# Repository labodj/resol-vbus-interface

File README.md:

# RESOL VBus interface

I designed this board to connect my **RESOL DeltaSol CS Plus** solar controller to
ESPHome and Home Assistant, with hardware for both receiving and transmitting
VBus messages.

Both versions use a socketed **LOLIN D1 mini or S3 Mini**, a 5 V supply and the same RX/TX firmware pin mapping. Choose the board by how the controller and ESP must be grounded.

| | Isolated (Rev E design files) | ECO Rev A |
|---|---|---|
| Power and UART | RECOM isolated DC/DC, bus-side regulator and digital isolator | Receiver and TX logic run from the module’s 3.3 V rail |
| Grounding | ESP/USB ground is separated from the VBus circuit | USB, J1 ground and the negative output of the VBus bridge are connected |
| Assembly | 35 SMT components | 26 SMT components |
| Test status | D1 mini and S3 Mini tested on reworked Rev D; S3 Mini in service for weeks on a DeltaSol CS Plus | CAD checks passed; first assembled-board and field tests are pending |
| KiCad and schematic | [Project](hardware/rev-e/Resol_VBus_RevE.kicad_pro) · [PDF](docs/schematic.pdf) | [Project](hardware/eco-rev-a/RESOL_VBus_ECO_RevA.kicad_pro) · [PDF](hardware/eco-rev-a/RESOL_VBus_ECO_RevA.pdf) |
| Fabrication | [Gerber ZIP](fabrication/Resol_VBus_RevE_Gerbers.zip) · [BOM](fabrication/bom.csv) · [CPL](fabrication/cpl.csv) | [Gerber + stencil ZIP](fabrication/eco-rev-a/RESOL_VBus_ECO_RevA_Gerbers.zip) · [BOM](hardware/eco-rev-a/BOM.csv) · [CPL](fabrication/eco-rev-a/cpl.csv) |

Choose the isolated board when the grounding of the controller or a USB-connected PC is unknown. Choose ECO when a common ground is acceptable. On both boards, power from **J1 or USB, one source at a time**. J1 and J2 use identical connectors; label the power and VBus cables.

| KiCad 3D view | Isolated Rev E | ECO Rev A |
|---|---|---|
| Front |  |  |
| Back |  |  |

The photograph below shows the earlier isolated prototype used in the installation.

## Build notes

- **Isolated:** [prototype release](https://github.com/labodj/resol-vbus-interface/releases/tag/rev-e-prototype-1), [fabrication](docs/fabrication.md), [assembly](docs/assembly.md) and [circuit description](docs/circuit.md).
- **ECO:** [fabrication package and checks](fabrication/eco-rev-a/README.md), [wiring and first power-up](hardware/eco-rev-a/README.md).

## Rev E at a glance

- Two layers, **64 x 50 mm**, with SMD parts on the front.
- Isolated power, RX and TX, independent of the VBus supply level.
- TX stays off during startup and low isolated-supply voltage.
- Replaceable ESP module and accessible test points.
- JST XH **B2B-XH-A, 2.50 mm** connectors for both external power and VBus.
- TS391RIYLT receiver with hysteresis and input filtering.

**J1 is the 5 V input; J2 is VBus.** The connectors are identical, so label the
cables. Use either USB power or external 5 V, **never both at once**. Keep
`GND` and `GND_ISO` separate. This is a low-voltage interface, not a mains input.

## Field experience

The target controller is a DeltaSol CS Plus running firmware 1.11, with an
approximately 20 cm VBus cable.

The photographed board is the isolated Rev D with the comparator wiring corrected by hand. Both modules worked on this board. The [validation record](docs/validation.md) describes the correction in the later isolated layouts and the checks on the published Rev E files.

## Firmware

VBus uses UART at **9600 baud, 8N1, non-inverted**. TX must idle HIGH; driving it
LOW enables the bus sink once the bus-side supervisor releases the TX inhibit. Firmware must wait
for a bus grant before transmitting.

| Module | RX GPIO | TX GPIO | Observed on reworked Rev D |
|---|---:|---:|---|
| LOLIN D1 mini v4.0.0 (ESP8266) | 13 | 12 | Tested and working |
| LOLIN S3 Mini v1.0.0 | 11 | 13 | In service for weeks |

I am developing the ESPHome TX support separately. This repository contains
the hardware, not a ready-to-flash firmware image. It does not imply that the
standard ESPHome VBus component already supports transmitting settings.

## Editing the design

Install KiCad 10 or newer with its standard libraries and open the `.kicad_pro`
file. Project libraries use relative paths. The optional RECOM 3D model is not
included; a missing model affects the 3D view only. See [third-party notices](THIRD_PARTY.md).

The [maintenance notes](docs/manual-review.md) explain test-point exclusions
and the checks to run after changes.

## Citation

If you use this design in a publication, cite it using the [project citation metadata](CITATION.cff). Include the board revision so readers can identify the circuit you used.

## Background and license

My original design drew on the [ESPHome VBus documentation](https://esphome.io/components/vbus/)
and [FatBeard's VBus PCB project](https://github.com/FatBeard/vbus-arduino-library/tree/master/pcb).
This is an independent project, without endorsement by RESOL, ESPHome or LOLIN.
Their names and trademarks remain theirs.

Original hardware: **CERN-OHL-P-2.0**; documentation: **CC-BY-4.0**; scripts:
**MIT**. KiCad library data retains **CC-BY-SA-4.0 with the KiCad library exception**.
See [LICENSE.md](LICENSE.md) and [third-party notices](THIRD_PARTY.md).

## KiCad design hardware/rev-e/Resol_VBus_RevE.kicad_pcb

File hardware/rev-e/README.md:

# RESOL VBus isolated interface, Rev E

The RECOM converter and the UART isolator separate the controller-side circuit from the ESP supply and USB ground. Both external 5 V and USB can power the interface. Use one source at a time.

Both the D1 mini and the S3 Mini worked on the isolated Rev D after the comparator wiring rework. The S3 Mini has operated for weeks on a DeltaSol CS Plus. The published Rev E files have their own [CAD validation record](../../docs/validation.md).

| Front | Back |
|---|---|
|  |  |

[KiCad project](Resol_VBus_RevE.kicad_pro) · [Schematic](../../docs/schematic.pdf) · [Fabrication files](../../docs/fabrication.md) · [Assembly guide](../../docs/assembly.md)

The [ECO Rev A](../eco-rev-a/README.md) uses the module’s 3.3 V supply and a shared ground. It has its own fabrication package and is awaiting hardware testing.

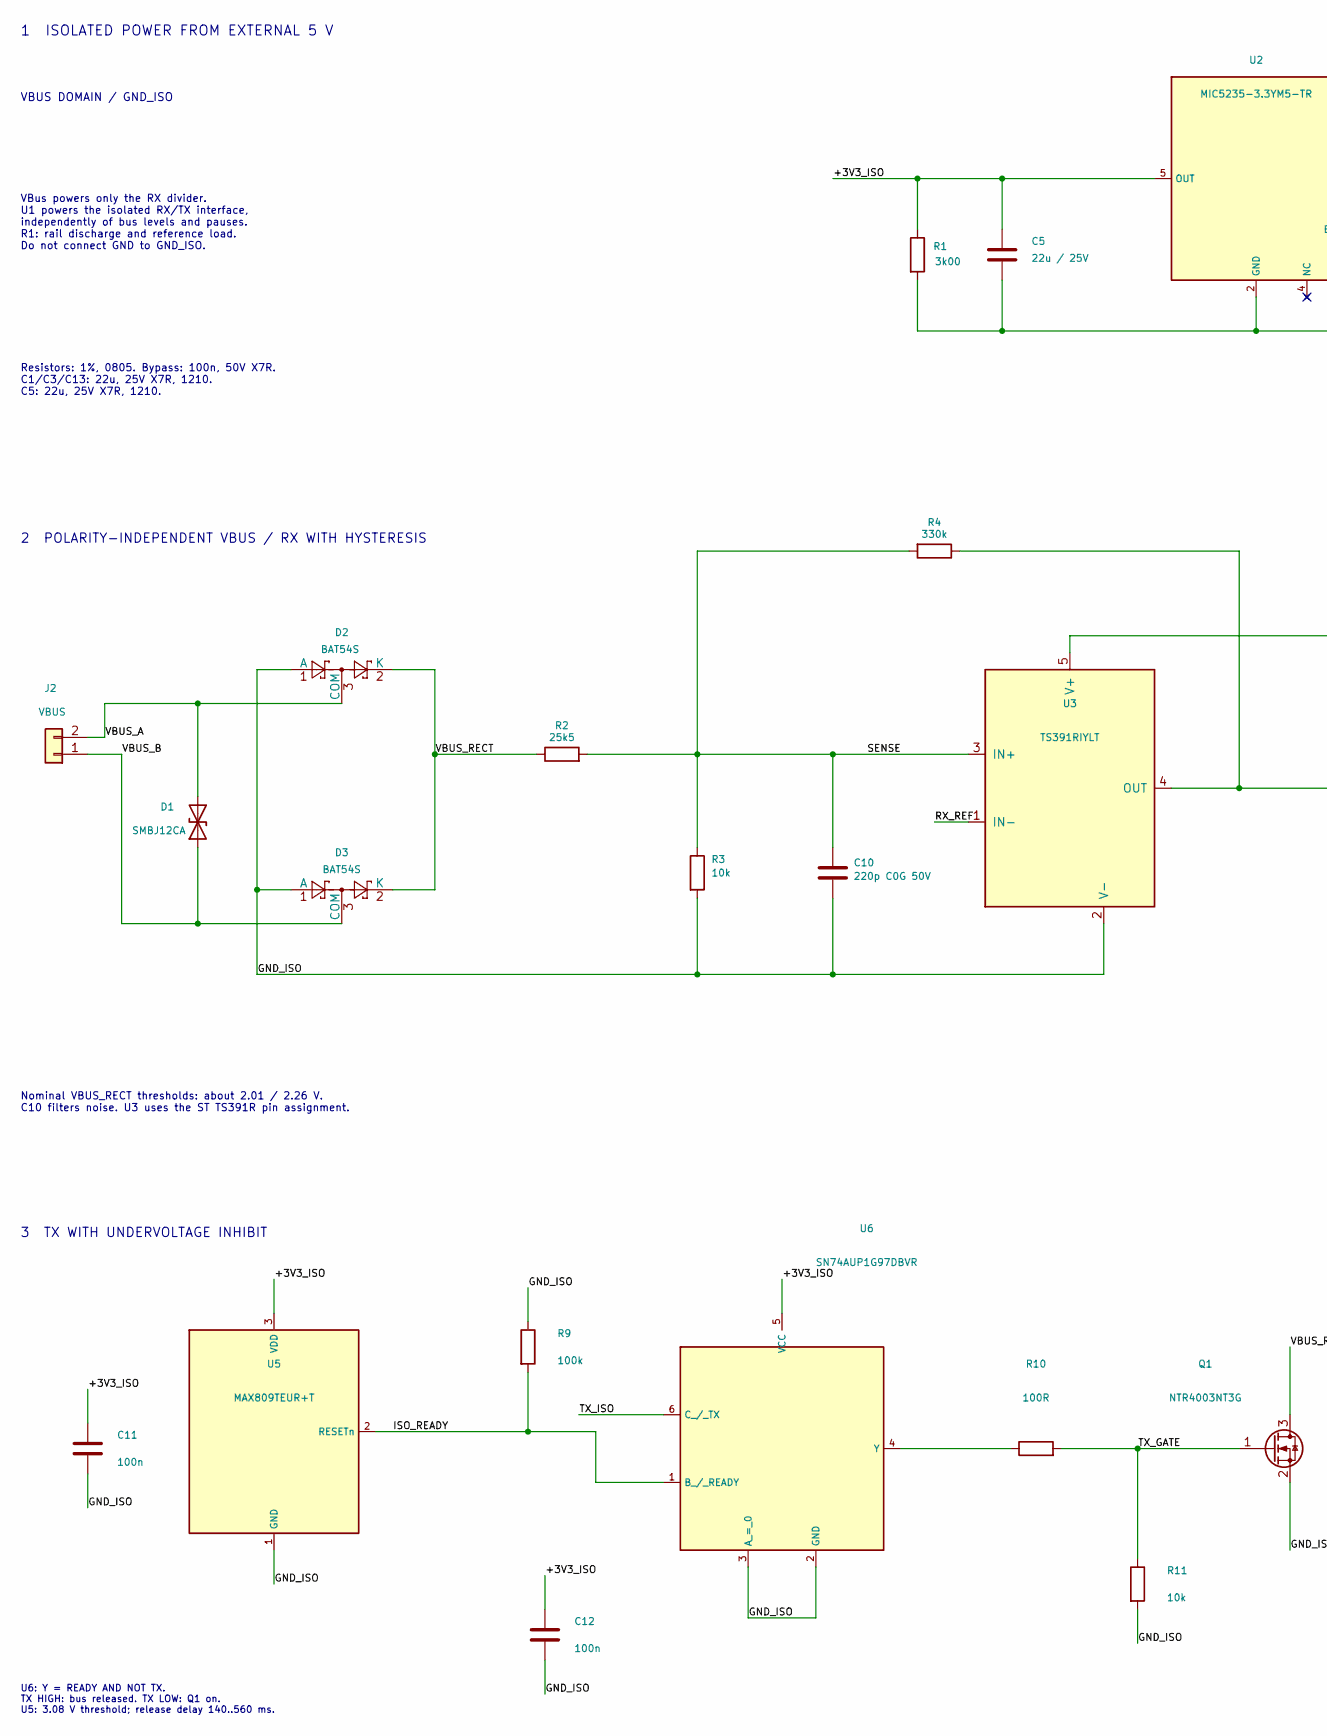
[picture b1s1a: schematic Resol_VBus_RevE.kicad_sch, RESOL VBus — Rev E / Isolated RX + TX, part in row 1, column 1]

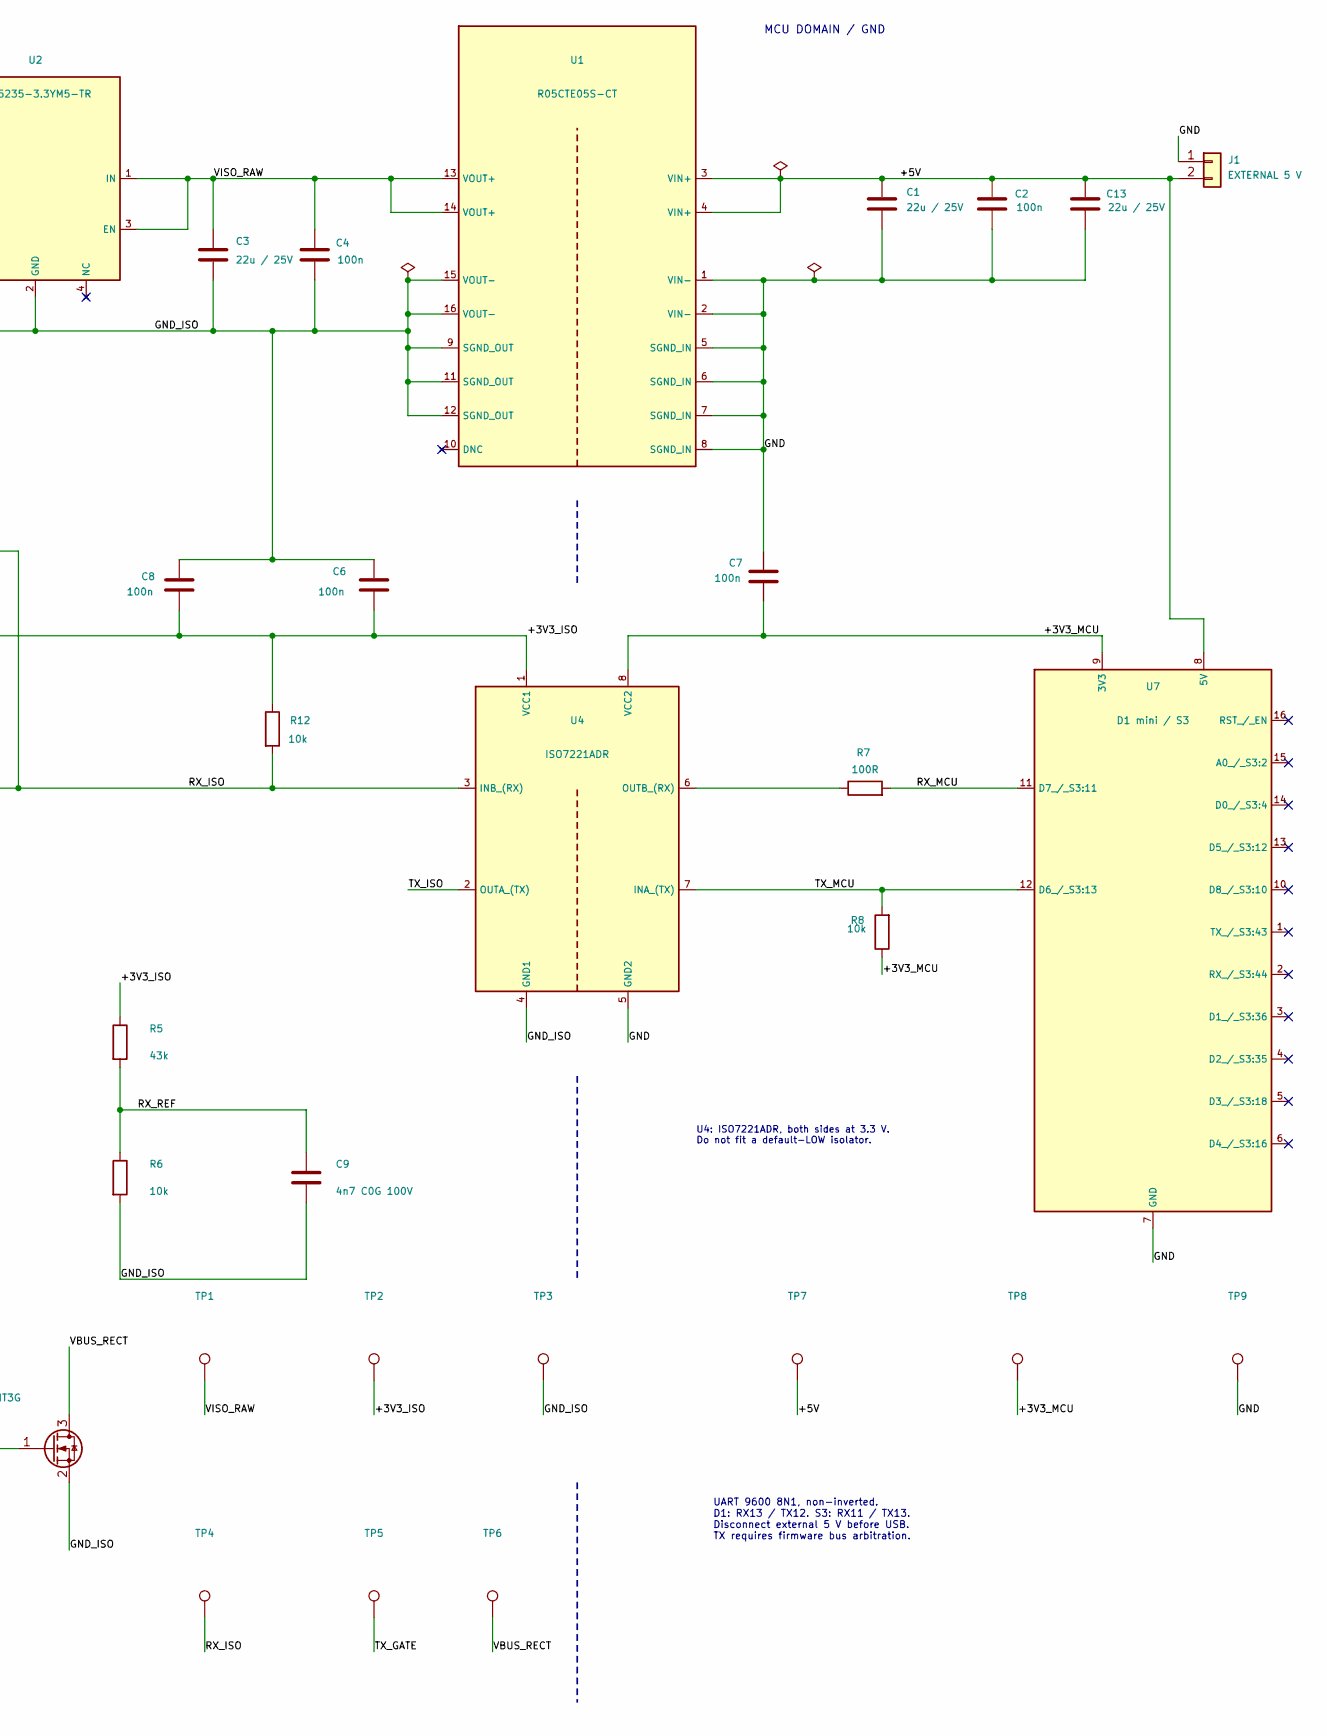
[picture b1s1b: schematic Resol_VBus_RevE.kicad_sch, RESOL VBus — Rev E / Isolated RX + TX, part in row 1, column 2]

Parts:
C1, C3, C5, C13: 22u / 25V; C_1210_3225Metric; MPN CL32B226KAJNNNE
C2, C4, C6, C7, C8, C11, C12: 100n; C_0805_2012Metric; MPN CC0805KRX7R9BB104
C9: 4n7 C0G 100V; C_0805_2012Metric; MPN C0805C472J1GACTU
C10: 220p C0G 50V; C_0805_2012Metric; MPN C0805C221J5GACTU
D1: SMBJ12CA; D_SMB; MPN SMBJ12CA-E3/52
D2, D3: BAT54S; SOT-23; MPN BAT54SQ-7-F
J1: EXTERNAL 5 V; JST_XH_B2B-XH-A_1x02_P2.50mm_Vertical; MPN B2B-XH-A
J2: VBUS; JST_XH_B2B-XH-A_1x02_P2.50mm_Vertical; MPN B2B-XH-A
Q1: NTR4003NT3G; SOT-23; MPN NTR4003NT3G
R1: 3k00; R_0805_2012Metric; MPN RC0805FR-073KL
R2: 25k5; R_0805_2012Metric; MPN RC0805FR-0725K5L
R3, R6, R8, R11, R12: 10k; R_0805_2012Metric; MPN RC0805FR-0710KL
R4: 330k; R_0805_2012Metric; MPN RC0805FR-07330KL
R5: 43k; R_0805_2012Metric; MPN RC0805FR-0743KL
R7, R10: 100R; R_0805_2012Metric; MPN RC0805FR-07100RL
R9: 100k; R_0805_2012Metric; MPN RC0805FR-07100KL
TP1: VISO_RAW; TestPoint_Pad_D1.0mm
TP2: +3V3_ISO; TestPoint_Pad_D1.0mm
TP3: GND_ISO; TestPoint_Pad_D1.0mm
TP4: RX_ISO; TestPoint_Pad_D1.0mm
TP5: TX_GATE; TestPoint_Pad_D1.0mm
TP6: VBUS_RECT; TestPoint_Pad_D1.0mm
TP7: +5V; TestPoint_Pad_D1.0mm
TP8: +3V3_MCU; TestPoint_Pad_D1.0mm
TP9: GND; TestPoint_Pad_D1.0mm
U1: R05CTE05S-CT; RECOM_R05CTE05S; MPN R05CTE05S-CT
U2: MIC5235-3.3YM5-TR; SOT-23-5; MPN MIC5235-3.3YM5-TR
U3: TS391RIYLT; SOT-23-5; MPN TS391RIYLT
U4: ISO7221ADR; SOIC-8_3.9x4.9mm_P1.27mm; MPN ISO7221ADR
U5: MAX809TEUR+T; SOT-23; MPN MAX809TEUR+T
U6: SN74AUP1G97DBVR; SOT-23-6; MPN SN74AUP1G97DBVR
U7: D1 mini / S3; Wemos_D1_mini_2x08

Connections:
/+3V3_ISO: C5.1, C6.1, C8.1, C11.1, C12.1, R1.1, R5.1, R12.1, TP2.1 (1_1), U2.5 (OUT), U3.5 (V+), U4.1 (VCC1), U5.3 (VDD), U6.5 (VCC)
/+3V3_MCU: C7.1, R8.1, TP8.1 (1_1), U4.8 (VCC2), U7.9 (3V3)
/+5V: C1.1, C2.1, C13.1, J1.2, TP7.1 (1_1), U1.3 (VIN+), U1.4 (VIN+), U7.8 (5V)
/GND: C1.2, C2.2, C7.2, C13.2, J1.1, TP9.1 (1_1), U1.1 (VIN-), U1.2 (VIN-), U1.5 (SGND_IN), U1.6 (SGND_IN), U1.7 (SGND_IN), U1.8 (SGND_IN), U4.5 (GND2), U7.7 (GND)
/GND_ISO: C3.2, C4.2, C5.2, C6.2, C8.2, C9.2, C10.2, C11.2, C12.2, D2.1 (A), D3.1 (A), Q1.2 (S), R1.2, R3.2, R6.2, R9.1, R11.2, TP3.1 (1_1), U1.9 (SGND_OUT), U1.11 (SGND_OUT), U1.12 (SGND_OUT), U1.15 (VOUT-), U1.16 (VOUT-), U2.2 (GND), U3.2 (V-), U4.4 (GND1), U5.1 (GND), U6.2 (GND), U6.3 (A_=_0)
/ISO_READY: R9.2, U5.2 (RESETn), U6.1 (B_/_READY)
/RX_ISO: R4.1, R12.2, TP4.1 (1_1), U3.4 (OUT), U4.3 (INB_(RX))
/RX_MCU: R7.2, U7.11 (D7_/_S3:11)
/RX_REF: C9.1, R5.2, R6.1, U3.1 (IN-)
/SENSE: C10.1, R2.2, R3.1, R4.2, U3.3 (IN+)
/TX_GATE: Q1.1 (G), R10.2, R11.1, TP5.1 (1_1)
/TX_ISO: U4.2 (OUTA_(TX)), U6.6 (C_/_TX)
/TX_MCU: R8.2, U4.7 (INA_(TX)), U7.12 (D6_/_S3:13)
/VBUS_A: D1.2 (A2), D2.3 (COM), J2.2
/VBUS_B: D1.1 (A1), D3.3 (COM), J2.1
/VBUS_RECT: D2.2 (K), D3.2 (K), Q1.3 (D), R2.1, TP6.1 (1_1)
/VISO_RAW: C3.1, C4.1, TP1.1 (1_1), U1.13 (VOUT+), U1.14 (VOUT+), U2.1 (IN), U2.3 (EN)
unnamed: R7.1, U4.6 (OUTB_(RX))
unnamed: R10.1, U6.4 (Y)

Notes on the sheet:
2 POLARITY-INDEPENDENT VBUS / RX WITH HYSTERESIS
Resistors: 1%, 0805. Bypass: 100n, 50V X7R. C1/C3/C13: 22u, 25V X7R, 1210. C5: 22u, 25V X7R, 1210.
UART 9600 8N1, non-inverted. D1: RX13 / TX12. S3: RX11 / TX13. Disconnect external 5 V before USB. TX requires firmware bus arbitration.
3 TX WITH UNDERVOLTAGE INHIBIT
Nominal VBUS_RECT thresholds: about 2.01 / 2.26 V. C10 filters noise. U3 uses the ST TS391R pin assignment.
MCU DOMAIN / GND
VBUS DOMAIN / GND_ISO
1 ISOLATED POWER FROM EXTERNAL 5 V
U4: ISO7221ADR, both sides at 3.3 V. Do not fit a default-LOW isolator.
U6: Y = READY AND NOT TX. TX HIGH: bus released. TX LOW: Q1 on. U5: 3.08 V threshold; release delay 140..560 ms.
VBus powers only the RX divider. U1 powers the isolated RX/TX interface, independently of bus levels and pauses. R1: rail discharge and reference load. Do not connect GND to GND_ISO.

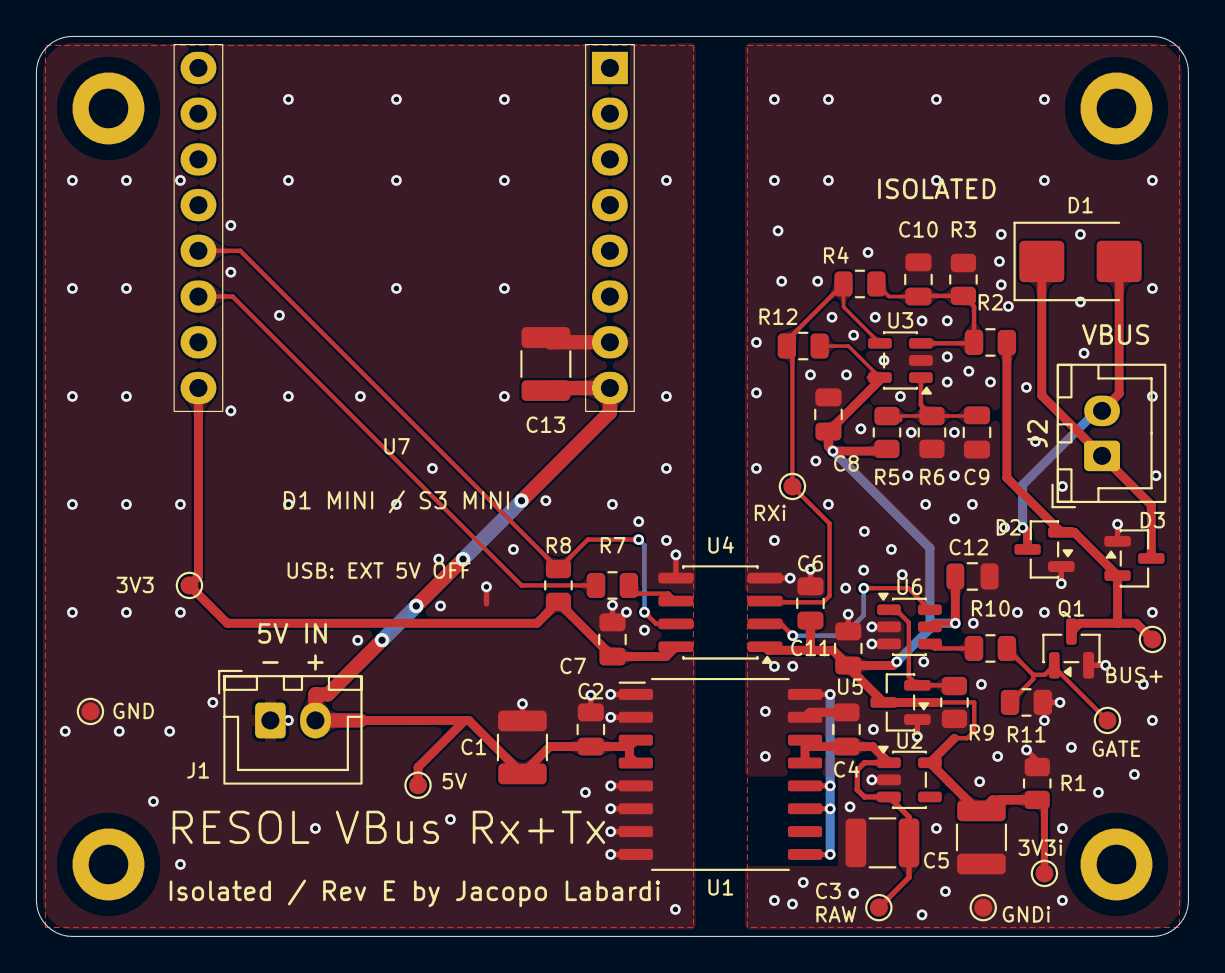
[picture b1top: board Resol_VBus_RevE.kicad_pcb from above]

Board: 2 copper layers, 64.0 x 50.0 mm, 51 parts (0 on the bottom side), 19 nets.

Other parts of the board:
H1, H2, H3, H4: M2 / 2.2 mm PTH; MountingHole_2.2mm_M2_Plated_Isolated

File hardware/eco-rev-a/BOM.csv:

"Reference","Value","Footprint","Manufacturer","MPN"
"C5","22u / 25V","Capacitor_SMD:C_1210_3225Metric","Samsung Electro-Mechanics","CL32B226KAJNNNE"
"C6","100n","Capacitor_SMD:C_0805_2012Metric","Yageo","CC0805KRX7R9BB104"
"C9","4n7 C0G 100V","Capacitor_SMD:C_0805_2012Metric","KEMET","C0805C472J1GACTU"
"C10","220p C0G 50V","Capacitor_SMD:C_0805_2012Metric","KEMET","C0805C221J5GACTU"
"C11","100n","Capacitor_SMD:C_0805_2012Metric","Yageo","CC0805KRX7R9BB104"
"C12","100n","Capacitor_SMD:C_0805_2012Metric","Yageo","CC0805KRX7R9BB104"
"C13","22u / 25V","Capacitor_SMD:C_1210_3225Metric","Samsung Electro-Mechanics","CL32B226KAJNNNE"
"D1","SMBJ12CA","Diode_SMD:D_SMB","Vishay","SMBJ12CA-E3/52"
"D2","BAT54S","Package_TO_SOT_SMD:SOT-23","Diodes Incorporated","BAT54SQ-7-F"
"D3","BAT54S","Package_TO_SOT_SMD:SOT-23","Diodes Incorporated","BAT54SQ-7-F"
"J1","EXTERNAL 5 V","Connector_JST:JST_XH_B2B-XH-A_1x02_P2.50mm_Vertical","JST","B2B-XH-A"
"J2","VBUS","Connector_JST:JST_XH_B2B-XH-A_1x02_P2.50mm_Vertical","JST","B2B-XH-A"
"Q1","NTR4003NT3G","Package_TO_SOT_SMD:SOT-23","onsemi","NTR4003NT3G"
"R2","25k5","Resistor_SMD:R_0805_2012Metric","Yageo","RC0805FR-0725K5L"
"R3","10k","Resistor_SMD:R_0805_2012Metric","Yageo","RC0805FR-0710KL"
"R4","330k","Resistor_SMD:R_0805_2012Metric","Yageo","RC0805FR-07330KL"
"R5","43k","Resistor_SMD:R_0805_2012Metric","Yageo","RC0805FR-0743KL"
"R6","10k","Resistor_SMD:R_0805_2012Metric","Yageo","RC0805FR-0710KL"
"R7","1k10","Resistor_SMD:R_0805_2012Metric","Yageo","RC0805FR-071K1L"
"R8","10k","Resistor_SMD:R_0805_2012Metric","Yageo","RC0805FR-0710KL"
"R9","100k","Resistor_SMD:R_0805_2012Metric","Yageo","RC0805FR-07100KL"
"R10","100R","Resistor_SMD:R_0805_2012Metric","Yageo","RC0805FR-07100RL"
"R11","10k","Resistor_SMD:R_0805_2012Metric","Yageo","RC0805FR-0710KL"
"R12","10k","Resistor_SMD:R_0805_2012Metric","Yageo","RC0805FR-0710KL"
"R14","1k","Resistor_SMD:R_0805_2012Metric","Yageo","RC0805FR-071KL"
"U3","TS391RIYLT","Package_TO_SOT_SMD:SOT-23-5","STMicroelectronics","TS391RIYLT"
"U5","MAX809TEUR+T","Package_TO_SOT_SMD:SOT-23","Analog Devices / Maxim","MAX809TEUR+T"
"U6","SN74AUP1G97DBVR","Package_TO_SOT_SMD:SOT-23-6","Texas Instruments","SN74AUP1G97DBVR"
"U7","D1 mini / S3","ResolVBusD:Wemos_D1_mini_2x08","LOLIN / WEMOS",""
